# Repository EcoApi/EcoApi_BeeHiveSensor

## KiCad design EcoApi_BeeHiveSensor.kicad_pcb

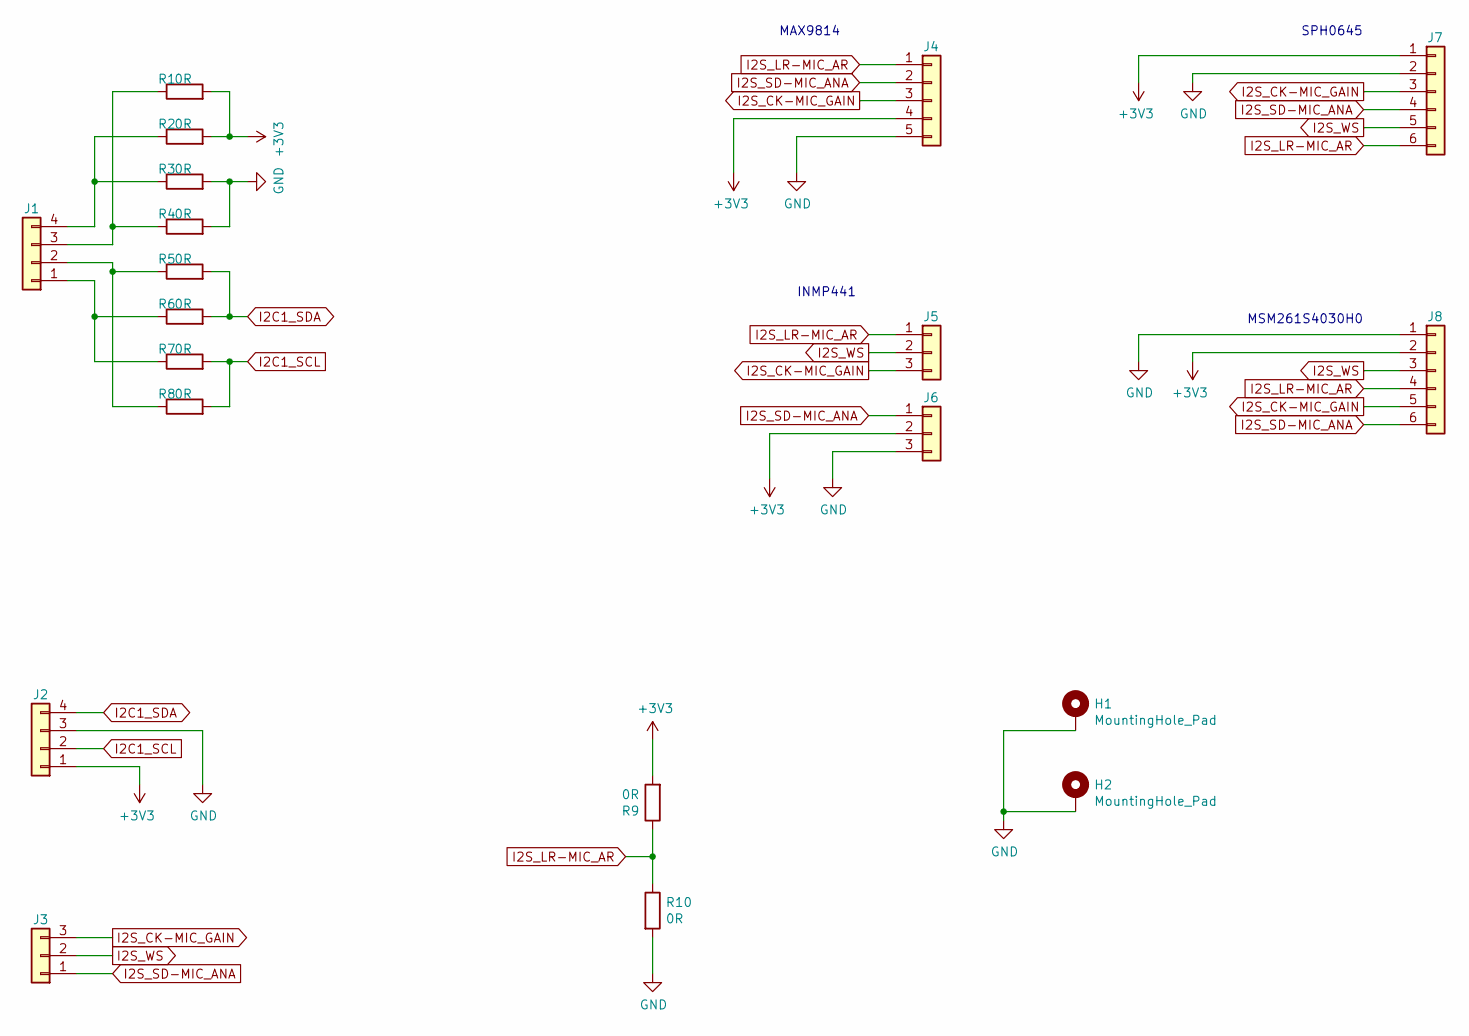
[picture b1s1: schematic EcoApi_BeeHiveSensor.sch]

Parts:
H1, H2: MountingHole_Pad; MountingHole_2.7mm_M2.5_DIN965_Pad
J1, J2: Conn_01x04; PinSocket_1x04_P2.54mm_Vertical
J3, J5, J6: Conn_01x03; PinSocket_1x03_P2.54mm_Vertical
J4: Conn_01x05; PinSocket_1x05_P2.54mm_Vertical
J7, J8: Conn_01x06; PinSocket_1x06_P2.54mm_Vertical
R1, R2, R3, R4, R5, R6, R7, R8, R9, R10: 0R; R_0603_1608Metric

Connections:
+3V3: J2.1, J4.4, J6.2, J7.1, J8.2, R1.2, R2.2, R9.2
GND: H1.1, H2.1, J2.3, J4.5, J6.3, J7.2, J8.1, R3.2, R4.2, R10.2
I2C1_SCL: J2.2, R7.2, R8.2
I2C1_SDA: J2.4, R5.2, R6.2
I2S_CK-MIC_GAIN: J3.3, J4.3, J5.3, J7.3, J8.5
I2S_LR-MIC_AR: J4.1, J5.1, J7.6, J8.4, R9.1, R10.1
I2S_SD-MIC_ANA: J3.1, J4.2, J6.1, J7.4, J8.6
I2S_WS: J3.2, J5.2, J7.5, J8.3
unnamed: J1.1, R6.1, R7.1
unnamed: J1.2, R5.1, R8.1
unnamed: J1.3, R1.1, R4.1
unnamed: J1.4, R2.1, R3.1

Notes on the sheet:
SPH0645
MSM261S4030H0
MAX9814
INMP441

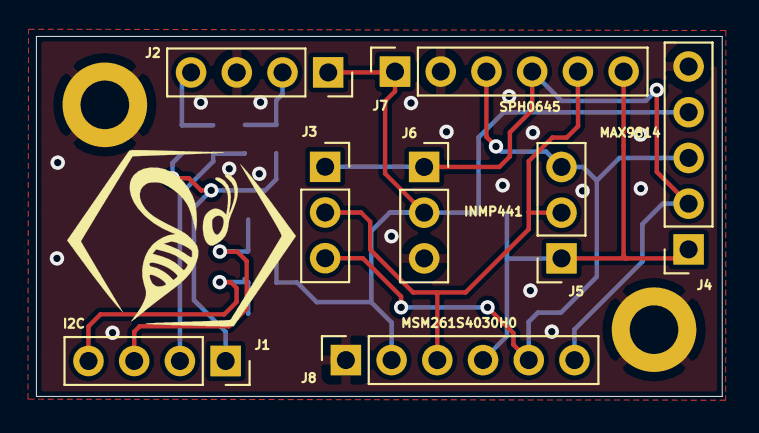
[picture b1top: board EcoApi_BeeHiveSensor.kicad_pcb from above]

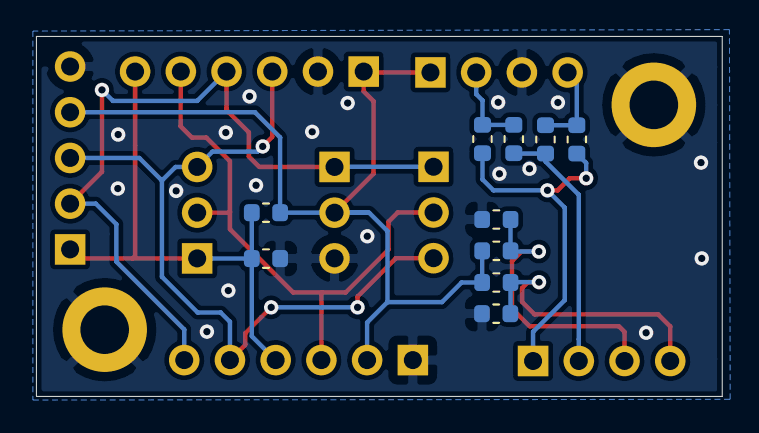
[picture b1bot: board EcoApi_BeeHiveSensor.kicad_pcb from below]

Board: 2 copper layers, 38.1 x 20.0 mm, 20 parts (10 on the bottom side), 12 nets.
